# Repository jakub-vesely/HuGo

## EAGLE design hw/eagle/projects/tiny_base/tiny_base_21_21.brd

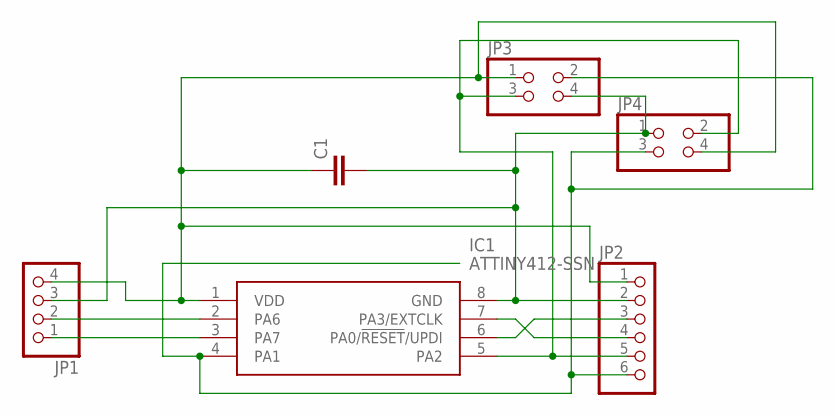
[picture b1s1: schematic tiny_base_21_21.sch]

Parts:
C1: C-EUC0805K; C0805K
IC1: ATTINY412-SSN; SOIC127P600X175-8N
JP1: PINHD-1X4; 1X04
JP2: PINHD-1X6; 1X06
JP3, JP4: PINHD-2X2; 2X02

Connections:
GND: C1.2, IC1.8 (GND), JP1.3, JP2.2, JP3.4, JP4.1
P0: IC1.2 (PA6), JP1.2
P1: IC1.3 (PA7), JP1.1
P4: IC1.7 (PA3/EXTCLK), JP2.4
SCL: IC1.5 (PA2), JP2.5, JP3.3, JP4.2
SDA: IC1.4 (PA1), JP2.6, JP3.2, JP4.3
UPDI: IC1.6 (PA0/!RESET!/UPDI), JP2.3
VDD: C1.1, IC1.1 (VDD), JP1.4, JP2.1, JP3.1, JP4.4

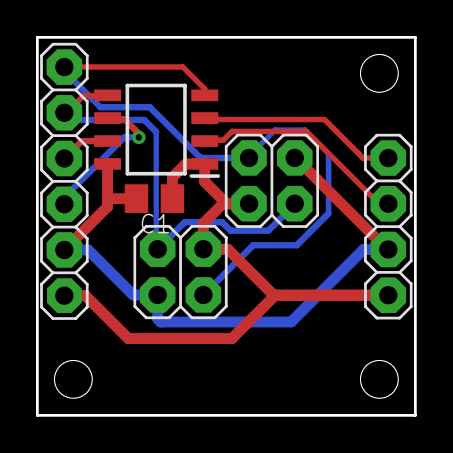
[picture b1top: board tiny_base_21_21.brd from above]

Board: 2 copper layers, 21.0 x 21.0 mm, 6 parts (0 on the bottom side), 8 nets.

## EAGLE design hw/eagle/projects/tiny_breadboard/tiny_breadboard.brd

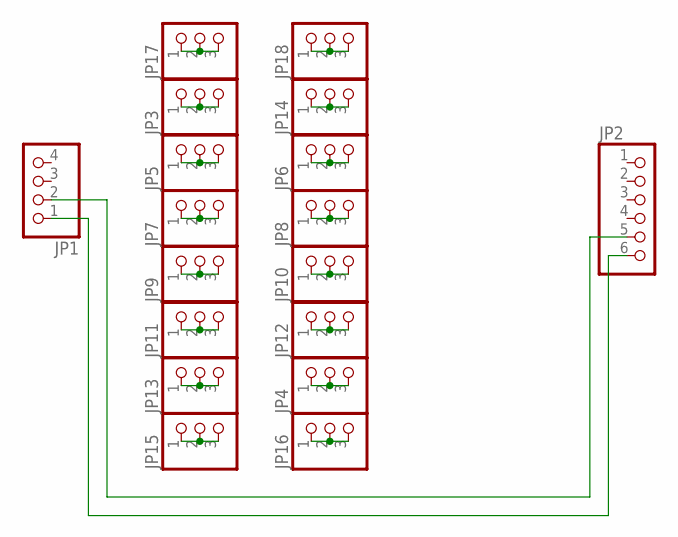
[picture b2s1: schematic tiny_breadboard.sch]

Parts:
JP1: PINHD-1X4; 1X04
JP2: PINHD-1X6; 1X06
JP3, JP4, JP5, JP6, JP7, JP8, JP9, JP10, JP11, JP12, JP13, JP14, JP15, JP16, JP17, JP18: PINHD-1X3; 1X03

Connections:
GND: JP1.2, JP2.5
unnamed: JP17.1, JP17.2, JP17.3
unnamed: JP15.1, JP15.2, JP15.3
unnamed: JP13.1, JP13.2, JP13.3
unnamed: JP11.1, JP11.2, JP11.3
unnamed: JP9.1, JP9.2, JP9.3
unnamed: JP7.1, JP7.2, JP7.3
unnamed: JP5.1, JP5.2, JP5.3
unnamed: JP3.1, JP3.2, JP3.3
unnamed: JP4.1, JP4.2, JP4.3
unnamed: JP6.1, JP6.2, JP6.3
unnamed: JP8.1, JP8.2, JP8.3
unnamed: JP10.1, JP10.2, JP10.3
unnamed: JP12.1, JP12.2, JP12.3
unnamed: JP14.1, JP14.2, JP14.3
unnamed: JP16.1, JP16.2, JP16.3
unnamed: JP18.1, JP18.2, JP18.3
VDD: JP1.1, JP2.6

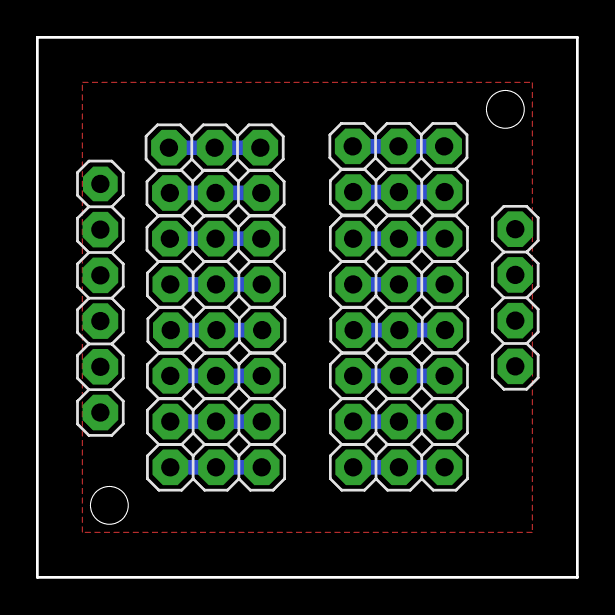
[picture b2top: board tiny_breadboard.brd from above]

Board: 2 copper layers, 30.0 x 30.0 mm, 18 parts (0 on the bottom side), 18 nets.

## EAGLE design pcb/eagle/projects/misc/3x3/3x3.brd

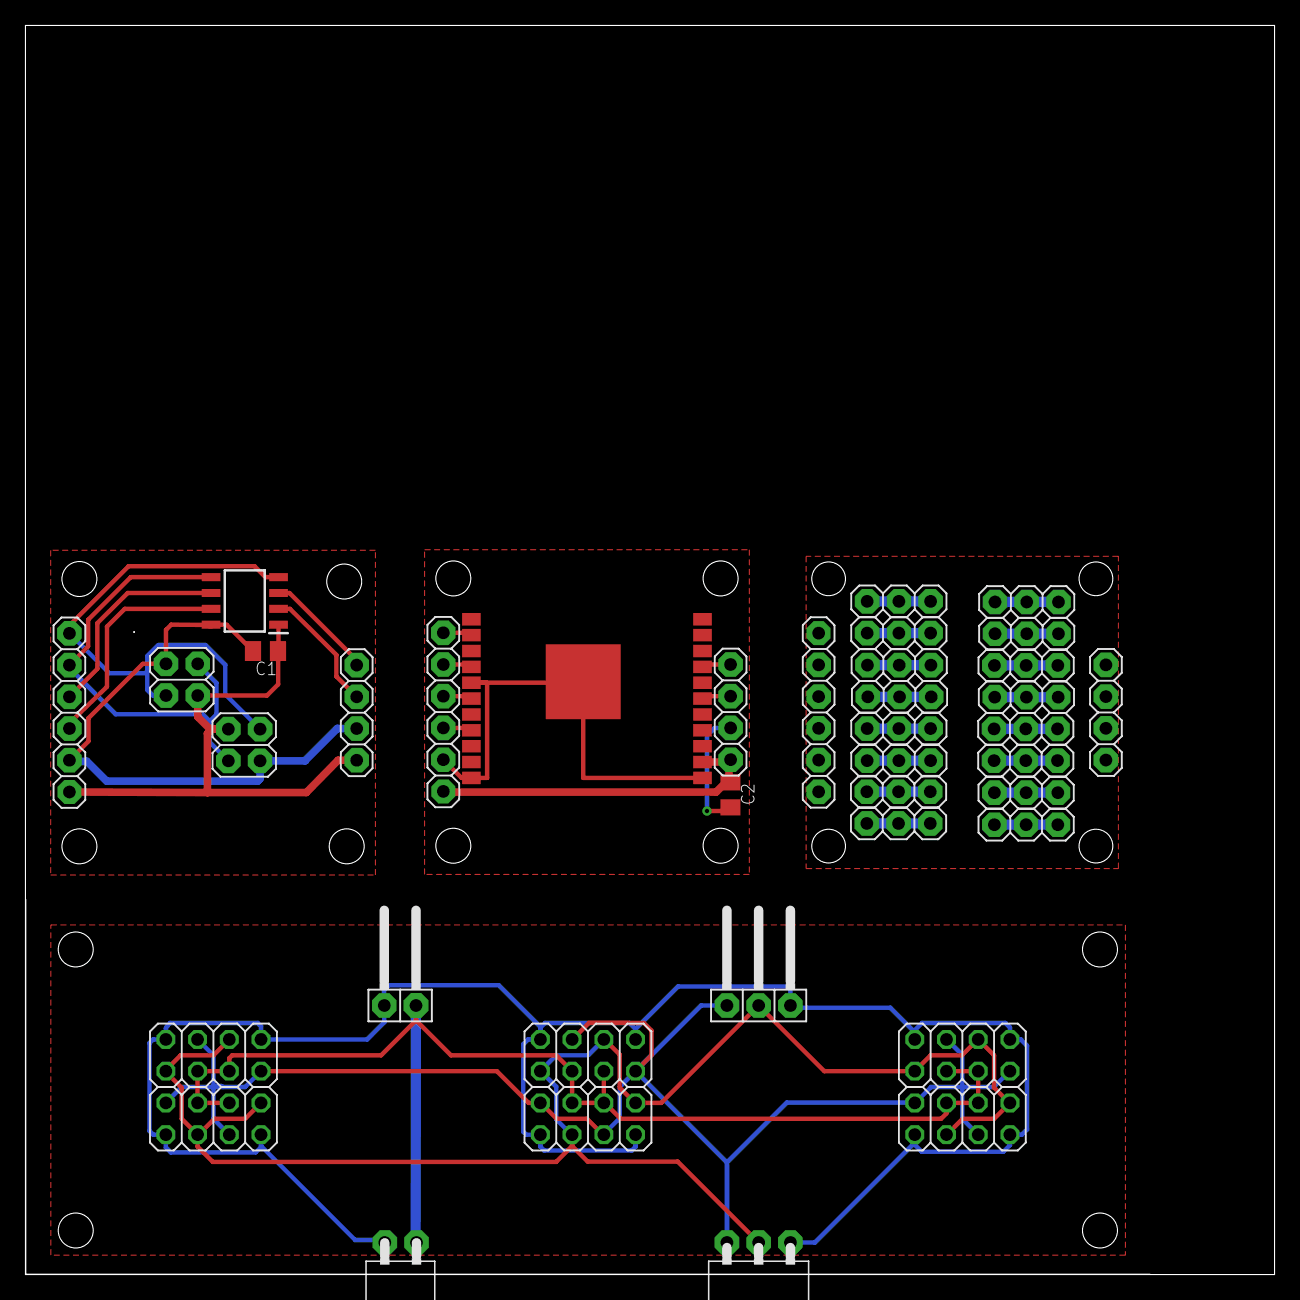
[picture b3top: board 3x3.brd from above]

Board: 2 copper layers, 100.0 x 100.0 mm, 38 parts (0 on the bottom side), 38 nets.

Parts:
C1, C2: C0805K
IC1: ATTINY412-SSN; SOIC127P600X175-8N
JP1, JP2, JP3, JP4, JP5, JP6: 2X04
JP7: 1X02/90
JP8: 1X03/90
JP9: 1X03/90F
JP10: 1X02/90F
JP11, JP15, JP17: 1X04
JP12, JP16, JP18: 1X06
JP13, JP14: 2X02
JP19, JP20, JP21, JP22, JP23, JP24, JP25, JP26, JP27, JP28, JP29, JP30, JP31, JP32, JP33, JP34: 1X03
U$1: ESP-WROOM-32-TINY-BLOCK

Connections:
GND: JP1.1, JP1.7, JP2.2, JP2.8, JP3.1, JP3.7, JP4.2, JP4.8, JP5.1, JP5.7, JP6.2, JP6.8, JP7.1, JP8.3, JP9.1, JP10.2
GND1: C1.2, IC1.8, JP11.3, JP12.2, JP13.4, JP14.1
GND2: C2.2, JP15.3, JP16.2, U$1.1, U$1.32, U$1.38, U$1.GND
GND3: JP17.2, JP18.5
unnamed: JP33.1, JP33.2, JP33.3
unnamed: JP31.1, JP31.2, JP31.3
unnamed: JP29.1, JP29.2, JP29.3
unnamed: JP27.1, JP27.2, JP27.3
unnamed: JP25.1, JP25.2, JP25.3
unnamed: JP23.1, JP23.2, JP23.3
unnamed: JP21.1, JP21.2, JP21.3
unnamed: JP19.1, JP19.2, JP19.3
unnamed: JP20.1, JP20.2, JP20.3
unnamed: JP22.1, JP22.2, JP22.3
unnamed: JP24.1, JP24.2, JP24.3
unnamed: JP26.1, JP26.2, JP26.3
unnamed: JP28.1, JP28.2, JP28.3
unnamed: JP30.1, JP30.2, JP30.3
unnamed: JP32.1, JP32.2, JP32.3
unnamed: JP34.1, JP34.2, JP34.3
P0: IC1.2, JP11.2
P1: IC1.3, JP11.1
P2: JP15.2, U$1.6
P3: JP15.1, U$1.8
P4: IC1.7, JP12.3
P5: JP16.3, U$1.35
SCL: JP1.2, JP1.5, JP2.4, JP2.7, JP3.2, JP3.5, JP4.4, JP4.7, JP5.2, JP5.5, JP6.4, JP6.7, JP8.1, JP9.3
SCL1: IC1.5, JP12.5, JP13.3, JP14.2
SCL2: JP16.5, U$1.31
SDA: JP1.3, JP1.8, JP2.1, JP2.6, JP3.3, JP3.8, JP4.1, JP4.6, JP5.3, JP5.8, JP6.1, JP6.6, JP8.2, JP9.2
SDA1: IC1.4, JP12.6, JP13.2, JP14.3
SDA2: JP16.6, U$1.29
UPDI: IC1.6, JP12.4
UPDI1: JP16.4, U$1.33
VCC: JP1.4, JP1.6, JP2.3, JP2.5, JP3.4, JP3.6, JP4.3, JP4.5, JP5.4, JP5.6, JP6.3, JP6.5, JP7.2, JP10.1
VCC1: C2.1, JP15.4, JP16.1, U$1.2
VCC2: JP17.1, JP18.6
VDD: C1.1, IC1.1, JP11.4, JP12.1, JP13.1, JP14.4

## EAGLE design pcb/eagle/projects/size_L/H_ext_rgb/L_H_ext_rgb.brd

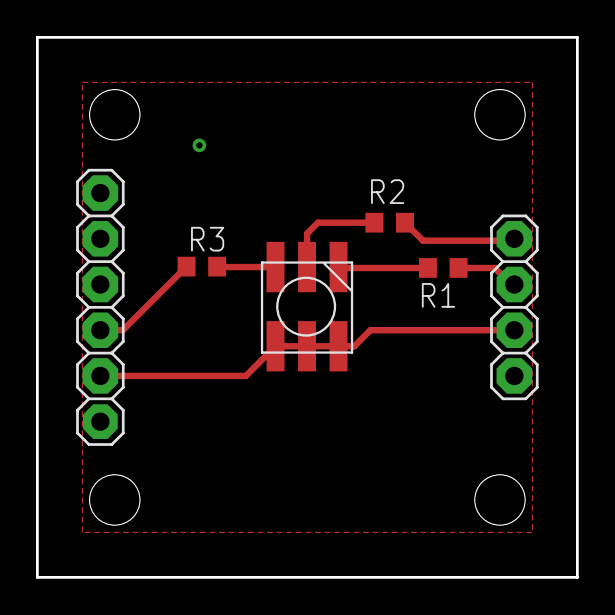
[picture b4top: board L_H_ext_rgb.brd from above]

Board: 2 copper layers, 30.0 x 30.0 mm, 6 parts (0 on the bottom side), 7 nets.

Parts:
JP1: 1X04
JP2: 1X06
R1, R2, R3: R0603
U$2: RGB_WW-FCE50TC-Q1

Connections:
GND: JP1.3, JP2.2, U$2.4, U$2.5, U$2.6
unnamed: R1.2, U$2.1
unnamed: R3.2, U$2.3
unnamed: R2.2, U$2.2
unnamed: JP1.1, R2.1
unnamed: JP1.2, R1.1
P4: JP2.3, R3.1

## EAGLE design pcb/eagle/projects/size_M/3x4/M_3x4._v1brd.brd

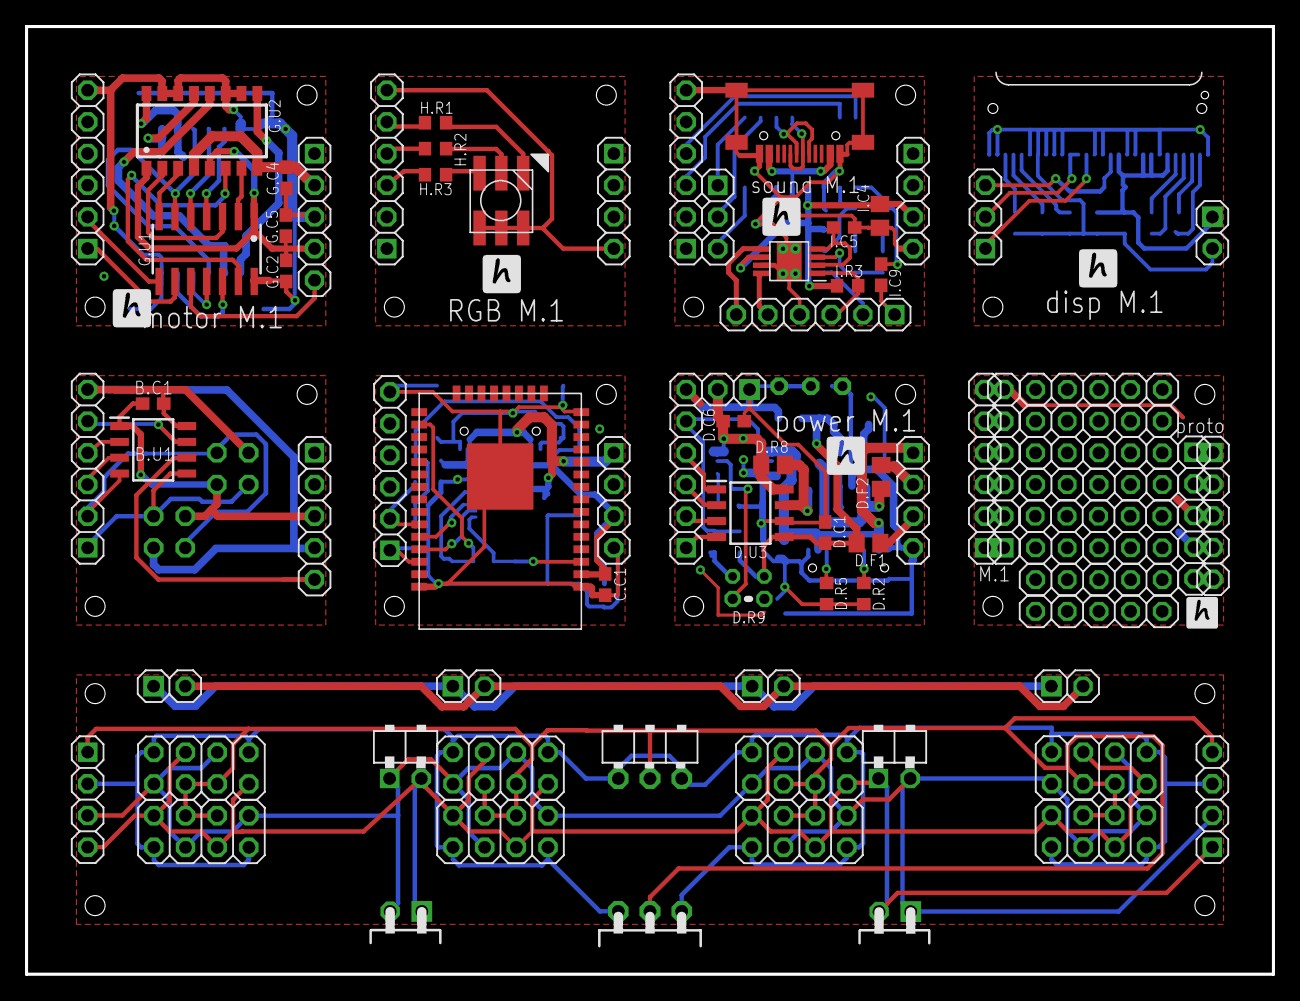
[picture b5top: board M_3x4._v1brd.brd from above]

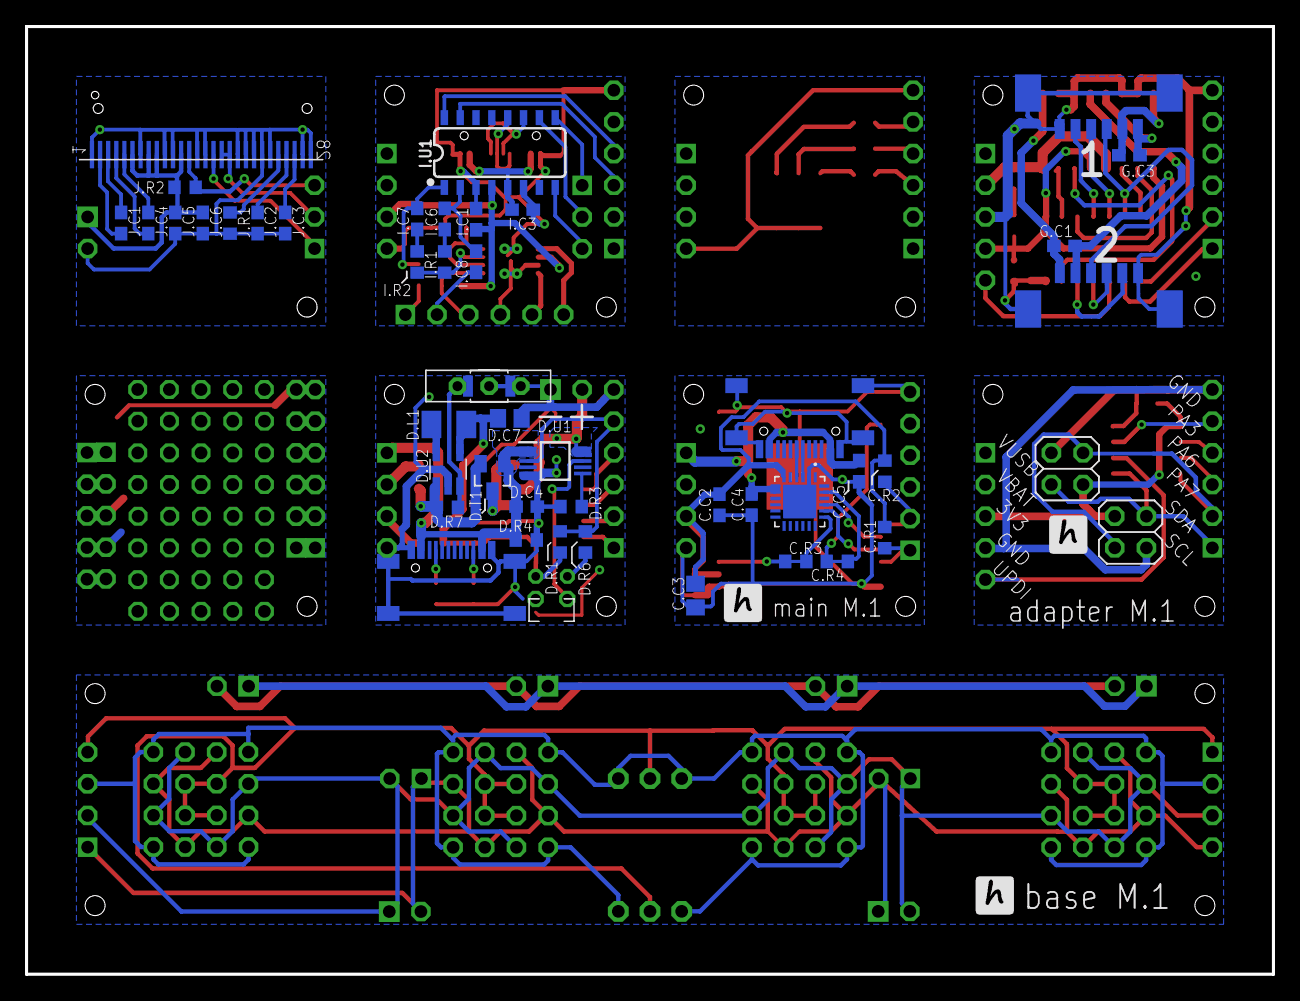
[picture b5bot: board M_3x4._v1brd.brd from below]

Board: 2 copper layers, 100.0 x 76.0 mm, 124 parts (46 on the bottom side), 114 nets.

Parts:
A.J1, A.J2, A.J3, A.J4, A.J5, A.J6, A.J11, A.J12: 2X04
A.J7, A.J14: 1X02/90
A.J8: 1X03/90
A.J9: 1X03/90F
A.J10, A.J13: 1X02/90F
A.J15, A.J16: 1X04
B.C1: 100n; C0603
B.J2: 1X06
B.J4: 2X02
B.J5: 1X05
B.U1: AT412; SOIC127P600X175-8N
C.C1, C.C2, C.C4: 100n; C0603
C.C3: 22u; C0805
C.C5: 10u; C0603
C.J2: 1X06
C.R1, C.R2: 2k2; R0603
C.R3, C.R4: 0; R0603
C.U1: TTGO-MICRO-32
D.C1: 100n; C0603
D.C4, D.C6: 4u7; C0603
D.C7: 22u; C0805
D.D1: LED_1.8
D.F1, D.F2: R0805
D.J2: 1X06
D.J3: 1X04
D.L1: 2u2; L3230M
D.LIPOL: 1X02
D.ON/OFF/RESET: SWITCH
D.R1, D.R4, D.R7: 100k; R0603
D.R2, D.R5: 5k1; R0603
D.R3: 1k; R0603
D.R6: 2k2; R0603
D.R8: 0.1; R0805
D.R9: TERM_10K; THERM
D.T1: FDV; SOT23
D.U1: MCP73833-AMI_UN; SOP50P490X110-10N
D.U2: LM3671_3.3; SOT32-5
D.U3: INA219AIDR; SOIC127P600X175-8N
G.C1, G.C2, G.C3: 100n; C0603
G.C4, G.C5: 4u7; C0603
G.J1: 1X06
G.J2: 1X05
G.J3, G.MOTO1: A1250WR-6
G.U1: AT414; SO14
G.U2: MX1508; SOP16
H.D1: RGB_WW-FCE50TC-Q1
H.J2, H.J4: 1X06
H.R1, H.R2, H.R3: 82; R0603
I.C1, I.C5, I.C6, I.C7, I.C8, I.C9: 100n; C0603
I.C3: 1u; C0603
I.C4: 10u (22u); C0805
I.J1: 1X03
I.J2: 1X06
I.J3: 1X04
I.J4: SSD_1306_STM32_OLED
I.J5: 1X02
I.R1, I.R2: 100k; R0603
I.R3: 10k; R0603
I.U1: WT2003S; SO16
I.U2: TPA6211; MSOP-POWERPAD-8
I.USB: USB-C
J.C1, J.C4: 1u; C0603
J.C2, J.C5: 2u2; C0603
J.C3: 2u; C0603
J.C6: 100n; C0603
J.J1: 1X03
J.R1: 390; R0603
J.R2: 100k; R0603
JB3: 2X02
JP1, JP2, JP3, JP4: 1X02
JP5, JP9: 1X04
JP6, JP7: 1X06
JP8, JP11: 1X05
U1: CP2104-F03-GM; QFN50P400X400X80-25N
U$1, U$2: USB-C
U$3, U$4, U$5, U$6, U$7, U$8, U$9, U$10: PINHD-1X5_AUTO; 1X5_AUTO

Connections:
3V3: B.C1.1, B.J4.4, B.J5.3, B.U1.1, JB3.1
3V3F: D.F1.2, D.J3.3
DCMD: I.J1.2, I.U1.10
FOTOA1: G.MOTO1.5, G.U1.4
FOTOA2: G.J3.5, G.U1.12
FOTOB1: G.MOTO1.4, G.U1.5
FOTOB2: G.J3.4, G.U1.11
GND: A.J1.1, A.J1.7, A.J2.2, A.J2.8, A.J3.1, A.J3.7, A.J4.2, A.J4.8, A.J5.1, A.J5.7, A.J6.2, A.J6.8, A.J8.1, A.J8.3, A.J9.1, A.J9.3, A.J11.1, A.J11.7, A.J12.2, A.J12.8, A.J15.2, A.J16.3
GND1: B.C1.2, B.J2.6, B.J4.1, B.J5.4, B.U1.8, JB3.4
GND2: C.C1.2, C.C2.2, C.C3.2, C.C4.1, C.C5.1, C.J2.6, C.U1.GND1, C.U1.GND2, C.U1.GND3, C.U1.GND4, C.U1.GND5, C.U1.GND6, C.U1.GND7, C.U1.GND8, C.U1.GND9, C.U1.GND10, C.U1.GND11, JP5.4, U1.2, U1.25, U$1.A1B12, U$1.B1A12, U$1.SH1, U$1.SH2, U$1.SH3, U$1.SH4
GND3: D.C1.1, D.C4.1, D.C6.1, D.C7.1, D.J2.6, D.J3.4, D.LIPOL.1, D.ON/OFF/RESET.P$2, D.ON/OFF/RESET.P$3, D.ON/OFF/RESET.P$5, D.R2.2, D.R3.1, D.R4.1, D.R5.2, D.R9.1, D.U1.5, D.U2.GND, D.U3.6, U$2.A1B12, U$2.B1A12, U$2.SH1, U$2.SH2, U$2.SH3, U$2.SH4
GND4: JP6.6, JP7.6, JP8.3, JP11.3
GND5: G.C2.1, G.C4.1, G.C5.1, G.J1.6, G.J2.3, G.J3.6, G.J3.$1, G.J3.$2, G.MOTO1.6, G.MOTO1.$1, G.MOTO1.$2, G.U1.14, G.U2.10, G.U2.11, G.U2.14, G.U2.15
GND6: H.D1.4, H.D1.5, H.D1.6, H.J2.6, JP9.4
GND7: H.J4.4, I.C1.2, I.C3.2, I.C4.1, I.C5.1, I.J2.6, I.J3.4, I.U1.3, I.U1.6, I.U2.7, I.U2.9, I.U2.P$10, I.U2.P$11, I.U2.P$12, I.U2.P$13, I.USB.A1B12, I.USB.B1A12, I.USB.SH1, I.USB.SH2, I.USB.SH3, I.USB.SH4
GND8: I.J4.P$1, I.J4.P$7, I.J4.P$10, I.J4.P$11, I.J4.P$14, I.J4.P$15, I.J4.P$19, I.J4.P$20, I.J4.P$21, I.J4.P$22, I.J4.P$23, I.J4.P$27, I.J4.P$28, I.J5.2, J.C2.1, J.C3.1, J.C5.1, J.C6.1, J.R1.1
IN+: D.C6.2, D.LIPOL.2, D.R8.2, D.U1.9, D.U1.10, D.U3.8
IN-: D.R8.1, D.T1.D, D.U3.7
INA1: G.U1.3, G.U2.2
INA2: G.U1.13, G.U2.6
INB1: G.U1.7, G.U2.3
INB2: G.U1.2, G.U2.7
MA1: G.C3.1, G.MOTO1.2, G.U2.16
MA2: G.C1.1, G.J3.2, G.U2.12
MB1: G.C3.2, G.MOTO1.1, G.U2.13
MB2: G.C1.2, G.J3.1, G.U2.9
M_V: G.C4.2, G.J2.2, G.U2.4, G.U2.8
unnamed: U1.4, U$1.A7
unnamed: U1.3, U$1.A6
unnamed: D.L1.1, D.U2.VOUT
unnamed: D.D1.1, D.R6.2
unnamed: D.ON/OFF/RESET.P$1, D.ON/OFF/RESET.P$4, D.R7.2, D.U2.SHDN
unnamed: D.R5.1, U$2.B5
unnamed: D.R2.1, U$2.A5
unnamed: D.R3.2, D.U1.6
unnamed: D.R9.2, D.U1.8
unnamed: JP6.5, JP7.5
unnamed: JP6.4, JP7.4
unnamed: JP6.3, JP7.3
unnamed: JP6.2, JP7.2
unnamed: JP6.1, JP7.1
unnamed: JP8.5, JP11.5
unnamed: JP8.2, JP11.2
unnamed: JP8.1, JP11.1
unnamed: H.D1.2, H.R2.2
unnamed: H.D1.1, H.R1.2
unnamed: H.D1.3, H.R3.2
unnamed: H.J2.5, H.R1.1
unnamed: H.J2.4, H.R2.1
unnamed: H.J2.3, H.R3.1
unnamed: I.J2.4, I.U1.16
unnamed: I.J2.3, I.U1.15
unnamed: I.U1.12, I.USB.A6, I.USB.B6
unnamed: I.U1.11, I.USB.A7, I.USB.B7
unnamed: I.C3.1, I.U1.5, I.USB.A4B9, I.USB.B4A9
unnamed: I.C6.1, I.C8.1, I.U1.2
unnamed: I.C7.1, I.C9.1, I.U1.1
unnamed: I.C5.2, I.U2.2, I.U2.4
unnamed: I.R1.2, I.R2.2, I.U2.3
unnamed: I.C6.2, I.R1.1
unnamed: I.C7.2, I.R2.1
unnamed: I.J4.P$24, J.R1.2
unnamed: I.J4.P$25, J.C2.2
unnamed: I.J4.P$2, J.C1.2
unnamed: I.J4.P$3, J.C1.1
unnamed: I.J4.P$4, J.C4.2
unnamed: I.J4.P$5, J.C4.1
unnamed: I.J4.P$26, J.C3.2
P0: D.J2.4, D.U3.1
P1: D.J2.3, D.U3.2
P4: D.J2.5, D.R1.2, D.R6.1, D.U1.3
PA1: I.J4.P$13, J.J1.3, J.R2.1
PA3: B.J2.5, B.U1.7
PA6: B.J2.4, B.U1.2
PA7: B.J2.3, B.U1.3
POWER: G.J3.3, G.MOTO1.3, G.U1.6
PROG: C.R4.1, C.R4.2, C.U1.IO0, U1.23
RESET: C.R3.1, C.R3.2, C.U1.EN, U1.19
RX: C.U1.TXD0, U1.20
SCL: A.J1.2, A.J1.5, A.J2.4, A.J2.7, A.J3.2, A.J3.5, A.J4.4, A.J4.7, A.J5.2, A.J5.5, A.J6.4, A.J6.7, A.J7.2, A.J10.1, A.J11.2, A.J11.5, A.J12.4, A.J12.7, A.J13.2, A.J14.1, A.J15.4, A.J16.1
SCL1: B.J2.1, B.J4.3, B.U1.5, JB3.2
SCL2: C.J2.1, C.R1.1, C.U1.IO22
SCL3: D.J2.1, D.U3.4
SCL4: G.J1.1, G.U1.9
SCL5: I.J4.P$16, J.J1.1
SDA: A.J1.3, A.J1.8, A.J2.1, A.J2.6, A.J3.3, A.J3.8, A.J4.1, A.J4.6, A.J5.3, A.J5.8, A.J6.1, A.J6.6, A.J7.1, A.J10.2, A.J11.3, A.J11.8, A.J12.1, A.J12.6, A.J13.1, A.J14.2, A.J15.3, A.J16.2
SDA1: B.J2.2, B.J4.2, B.U1.4, JB3.3
SDA2: C.J2.2, C.R2.1, C.U1.IO21
SDA3: D.J2.2, D.U3.3
SDA4: G.J1.2, G.U1.8
SDA5: I.J4.P$17, I.J4.P$18, J.J1.2
SDCLK: I.J1.1, I.U1.9
SDDAT: I.J1.3, I.U1.8
SHTDOWN: H.J4.3, I.R3.1, I.U2.1
TX: C.U1.RXD0, U1.21
UPDI: B.J5.5, B.U1.6
UPDI1: G.J2.5, G.U1.10
VBAT: JP1.2, JP2.2, JP3.2, JP4.2
VBATF: D.F2.2, D.J3.2
VCC: A.J1.4, A.J1.6, A.J2.3, A.J2.5, A.J3.4, A.J3.6, A.J4.3, A.J4.5, A.J5.4, A.J5.6, A.J6.3, A.J6.5, A.J8.2, A.J9.2, A.J11.4, A.J11.6, A.J12.3, A.J12.5, A.J15.1, A.J16.4
VCC1: C.C1.1, C.C2.1, C.C3.1, C.R1.2, C.R2.2, C.U1.3V3, JP5.3, U1.6
VCC2: G.C2.2, G.C5.2, G.J2.4, G.U1.1, G.U2.1, G.U2.5
VCC3: I.C1.1, I.C4.2, I.J3.3, I.R3.2, I.U1.4, I.U2.6
VCC4: D.C1.2, D.C7.2, D.D1.2, D.F1.1, D.L1.2, D.R1.1, D.U2.BP, D.U3.5
VDD1: JP8.4, JP11.4
VDD3: I.J4.P$6, I.J4.P$8, I.J4.P$9, I.J4.P$12, I.J5.1, J.C5.2, J.C6.2, J.R2.2
VMOT: D.F2.1, D.R7.1, D.T1.S, D.U2.VIN
VO+: H.J4.6, I.U2.5
VO-: H.J4.5, I.U2.8
VOUTL: H.J4.1, I.C9.2
VOUTR: H.J4.2, I.C8.2
VUSB: JP1.1, JP2.1, JP3.1, JP4.1
VUSB1: C.C4.2, C.C5.2, JP5.1, U1.7, U1.8, U$1.A4B9, U$1.B4A9
VUSB2: D.C4.2, D.J3.1, D.R4.2, D.T1.G, D.U1.1, D.U1.2, U$2.A4B9, U$2.B4A9

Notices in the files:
parts and their libraries:
esp32: Creative Commons Attribution-ShareAlike 4.0 International
